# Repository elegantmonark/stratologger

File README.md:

# Stratologger

I'm building an ESP32 payload to record changes in altitude, temperature and motion,
save each run to a microSD card, and show live readings on a small display. The
project combines a custom carrier PCB, removable sensor modules, firmware and a
PETG enclosure. The [contents](#contents) and [repository guide](#repository-guide)
point to the design files, software results and remaining hardware work.

**Author:** Trishan Biswas  
**Project started:** February 2026  
**Status:** Ongoing prototype development

| SL-1 carrier design | Initial system sketch |
|:---:|:---:|
|  |  |
| Current PCB design before manufacture. The ESP32 and sensor modules are not shown. | Original connections and display concept. The custom PCB replaces the drawn breadboard and perfboard stages. |

> [!IMPORTANT]
> **SL-1 is on fabrication hold.** The PCB socket map differs from the common
> 30-pin DOIT ESP32 DevKit V1. Exact module identification, dimensions, pin-map
> correction and rerouting are pending. Do not order the existing Gerber ZIP.
> See [the PCB audit](pcb/SL-1/review/PCB_AUDIT.md).

## Contents

- [SL-1 payload PCB](#sl-1-payload-pcb) · [PCB views](#pcb-views) · [Telemetry validation](#telemetry-validation)
- [Overview](#overview) · [Development](#development) · [Electrical integration](#electrical-integration) · [Display and firmware](#display-and-firmware)
- [Enclosure](#enclosure) · [Data format](#data-format) · [Limitations](#limitations) · [Repository guide](#repository-guide)
- [Next work](#next-work) · [Licence](#licence) · [Building the firmware](#building-the-firmware) · [Reproducing the checks](#reproducing-the-checks)

## SL-1 payload PCB

SL-1 is a two-layer, 90 by 70 mm carrier board. The ESP32 plugs into two 15-pin
female sockets, the AHT20/BMP280 connects through a four-pin male header, and the
GY-521 uses an eight-pin female socket. Four M3 mounting holes support the board
inside the enclosure.

The TFT and its onboard microSD socket mount in the lid and connect through a short
keyed 2x7 harness. Keeping the display separate leaves room for the modules below
and makes it replaceable. The separate TF-card reader is not used.

The [KiCad project](pcb/SL-1/Stratologger_SL1.kicad_pro),
[routed board](pcb/SL-1/Stratologger_SL1.kicad_pcb),
[assembly BOM](pcb/SL-1/manufacturing/assembly-bom.csv) and
[board guide](pcb/SL-1/README.md) are available for review. The design includes
ground planes, an ESP32 antenna keep-out, regulated 5 V input protection and a
single-cell battery-voltage divider.

The audited layout passes KiCad's filled-zone DRC, but the independent pin audit
found that its ESP32 socket assignments do not match the common 30-pin DOIT board.
Passing DRC does not establish the correct module pinout. The existing
[manufacturing outputs](pcb/SL-1/manufacturing/README.md) are historical files;
they will need regenerating after the socket map and routing are corrected.

## PCB views

These are KiCad screenshots of the SL-1 review design before manufacture.
The renders show the carrier, sockets and connectors. The plug-in ESP32, sensor
boards and remote TFT are absent, so these views do not confirm assembled fit.
F1 appears as a footprint because its solid 3D model is not shown.

### Routed layout

### Component renders

| Top view | Angled view |
|:---:|:---:|
|  |  |

## Telemetry validation

I checked the CSV serializer with 100,000 synthetic rows after finding a mismatch
between the checksum calculation and the saved decimal values. The earlier logger
calculated its checksum before rounding the measurements for CSV. That produced
512 checksum mismatches in the test. The revised serializer checks the values
actually written to the file and produced zero mismatches on the same inputs.

All 19 controlled cases met their stated expectations. They cover clean data,
altered measurements, missing and duplicated packets, reordered rows, timing faults,
invalid values, incomplete rows and counter rollover. One case demonstrates that
two changes can cancel under XOR and leave the checksum unchanged.

The [results and method](results/log-validation/README.md) include the
[fault matrix](results/log-validation/fault_matrix.csv), source hashes and limits.
These are software checks with synthetic inputs. Sensor accuracy, SD write
reliability and operation under physical stress still need bench measurements.

## Overview

The payload samples an AHT20/BMP280 combination board and an MPU6050 every 500 ms.
It records temperature, humidity, pressure, barometric altitude, acceleration and
angular velocity, together with packet numbers, timestamps and a checksum.

The work is split into four subsystems:

| Subsystem | Purpose | Current state |
|---|---|---|
| Electrical | Carrier PCB, removable modules and power distribution | SL-1 routed; fabrication held for socket-map correction and measured fit |
| Display | Landscape ST7789V TFT, screen button and onboard SD socket | UI and separate demo compile; physical display and harness checks pending |
| Mechanical | PETG enclosure, module retention, vents and access | Parametric source available; dimensions and printed fit unverified |
| Software | Acquisition, CSV logging, display rendering and host analysis | Firmware builds; synthetic log checks recorded; hardware captures pending |

No assembled payload, battery-endurance result or environmental test run is
currently published.

## Development

The project began in February 2026 with an ESP32, environmental sensing, an IMU,
removable storage and a local display. The first sketch outlined the connections,
screen concept and a path from prototyping to an enclosed payload.

The October firmware baseline brought together sensor acquisition, three display
screens, CSV logging and host validation. The electrical design then moved to the
SL-1 carrier so the modules could remain removable inside the enclosure.

The PCB review exposed the ESP32 socket-map mismatch despite clean routing checks.
The November software checks also exposed the checksum rounding fault described
above. Both findings are recorded in the
[development log](docs/development-log.md) and [validation record](docs/validation.md).

## Electrical integration

| Function | ESP32 pin |
|---|---:|
| I2C SDA / SCL | GPIO21 / GPIO22 |
| VSPI SCK / MOSI / MISO | GPIO18 / GPIO23 / GPIO19 |
| TFT CS / DC / RST | GPIO15 / GPIO2 / GPIO4 |
| SD CS | GPIO5 |
| Screen button | GPIO34 with external 10 kOhm pull-up |
| Battery measurement | GPIO35 through a 100 kOhm / 100 kOhm divider |

These are the intended GPIO functions. The carrier's physical socket positions
still need correcting against the exact ESP32 module. The
[wiring diagram](electrical/wiring-diagram.svg), [netlist](electrical/netlist.csv),
[BOM](electrical/bom.csv) and [assembly guide](electrical/assembly.md) document the
connections and power boundaries.

The environmental header runs `VDD, SDA, GND, SCL`. The display harness must be
matched to the signal names on the actual TFT board; fourteen-pin modules do not
share a universal pin order. TFT and SD use the same SPI bus with separate
chip-select lines.

Standalone power requires a protected single cell and a regulated 5 V supply.
The `5V POWER` input and measurement-only `BAT SENSE` input are separate.
A raw Li-ion or LiPo cell must not be connected directly to the 5 V input.

## Display and firmware

The 2.4-inch ST7789V runs in landscape at 320 by 240 pixels. A single button cycles
between live telemetry, IMU detail and system status. The live view combines an
altitude gauge, a 60-second trace, environmental readings and a simple artificial
horizon. The IMU page shows acceleration and angular-rate traces; the system page
shows raw readings and logging status.

The firmware separates sensor acquisition (`SensorManager`), file handling
(`TelemetryLogger`) and rendering (`DisplayManager`). TFT and SD transfers run
sequentially on the shared SPI bus. Boot faults are reported on the display when
available and through USB serial.

The [display subsystem guide](tft/README.md) includes the cable map and a separate
demo that supplies labelled synthetic values to the UI. Both firmware targets
compile; the display and finished harness still need checking on hardware.

## Enclosure

The [parametric OpenSCAD source](mechanical/enclosure.scad) defines a PETG base and
lid with a display aperture, button opening, sensor vents, PCB supports and USB
access. The carrier mounts in the base and the TFT mounts in the lid.

The dimensions are nominal. Final module heights, TFT mounting holes, battery
holder, cable bends and connector access must be measured before printing. The
[mechanical notes](mechanical/README.md) record the current assumptions.

## Data format

Logs are named `/LOG_001.CSV` through `/LOG_999.CSV` without overwriting an existing
file. Each row follows this schema:

```text
PACKET_ID,TIMESTAMP_MS,TEMP_C,HUMIDITY_PCT,PRESSURE_HPA,ALTITUDE_M,
ACCEL_X_MS2,ACCEL_Y_MS2,ACCEL_Z_MS2,GYRO_X_RADS,GYRO_Y_RADS,
GYRO_Z_RADS,CHECKSUM_HEX
```

The [format example](data/format-example.csv) contains synthetic values. New
hardware captures should include the configuration and conditions recorded in the
[run metadata template](data/run-metadata-template.yaml).

## Limitations

Barometric altitude depends on reference-pressure calibration. Acceleration during
motion distorts the gravity-derived roll and pitch display. The 2 Hz mission log
cannot support a meaningful vibration FFT above 1 Hz; that test needs a separate
acquisition rate.

The XOR checksum misses some combinations of changes. It detects simple corruption
and does not provide authentication. Firmware compilation and host checks also
leave sensor behaviour, supply stability, SD logging and enclosure fit unverified.
The [detailed limits](docs/limitations.md) and [test plan](docs/test-plan.md) cover
the remaining bench, thermal, vibration, impact and endurance work.

## Repository guide

| Location | Contents |
|---|---|
| [`pcb/`](pcb/README.md) | SL-1 KiCad source, review screenshots, audit and manufacturing status |
| [`electrical/`](electrical/assembly.md) | Wiring diagram, netlist, BOM and integration notes |
| [`tft/`](tft/README.md) | Display configuration, screen behaviour and cable map |
| [`mechanical/`](mechanical/README.md) | Parametric enclosure and fit assumptions |
| [`src/`](src/main.cpp) and [`include/`](include/config.h) | ESP32 firmware, display demo and shared configuration |
| [`tools/`](tools/validate_log.py) and [`tests/`](tests/test_repository.py) | CSV analysis, serializer fixture and repository checks |
| [`results/`](results/README.md) | Synthetic telemetry validation and recorded results |
| [`data/`](data/README.md) | CSV example and capture metadata template |
| [`docs/`](docs/development-log.md) | Development, architecture, validation, limits and test plans |
| [`hardware/`](hardware/README.md) | Physical build state and future hardware evidence |

## Next work

1. Confirm the exact ESP32 pinout and measure all module headers and body clearances.
2. Correct the SL-1 socket map and routing, repeat the electrical review and regenerate manufacturing files.
3. Assemble one board and check power, boot, sensors, TFT, SD and the display harness.
4. Fit the enclosure around the measured assembly and standalone power system.
5. Publish repeat captures and physical test results with their build configurations.

## Licence

The firmware, hardware documentation and mechanical source are released under the
Apache License 2.0 in [`LICENSE`](LICENSE).

## Building the firmware

Install the PlatformIO extension for Visual Studio Code and open the repository
root. Build, upload and open the serial monitor with:

```bash
pio run -e esp32dev
pio run -e esp32dev --target upload
pio device monitor
```

The [PlatformIO configuration](platformio.ini) selects the Arduino framework,
dependencies and TFT_eSPI pin settings. The installed library's `User_Setup.h`
does not need editing. To build the display-only demo:

```bash
pio run -e display-demo
```

## Reproducing the checks

Run the host checks from the repository root:

```bash
python -m unittest discover -s tools -p 'test_*.py' -v
python -m unittest discover -s tests -v
python tools/validate_log.py data/format-example.csv
```

The [telemetry validation instructions](results/log-validation/README.md#run-it-again)
explain how to compile the C++ serializer fixture and regenerate the controlled
cases and plots. PCB review and fabrication requirements are documented separately
in the [SL-1 board guide](pcb/SL-1/README.md).

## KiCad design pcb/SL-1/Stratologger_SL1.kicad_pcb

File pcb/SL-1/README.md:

# Stratologger SL-1 PCB

> **FABRICATION HOLD — 27 October 2026:** the existing ESP32 socket map does
> not match the common 30-pin DOIT DevKit V1. The exact module has not yet been
> confirmed. Do not order the existing Gerber ZIP. See [the audit](review/PCB_AUDIT.md).
> `release-status.json` blocks the fabrication script until the pin map and routing
> have been corrected and reviewed. The current board contains the new silkscreen logo.

SL-1 is a 90 by 70 mm, two-layer carrier board for the Stratologger payload. The
ESP32 and sensors remain replaceable, while the TFT and its onboard microSD socket
mount in the enclosure lid and connect through a short keyed harness.

## Board layout

- 30-pin ESP32 DevKit V1 on two 1x15 female sockets, with USB at the board edge.
- AHT20/BMP280 on a 1x4 male header ordered `VDD, SDA, GND, SCL`.
- GY-521 on a 1x8 female socket ordered `VCC, GND, SCL, SDA, XDA, XCL, AD0, INT`.
- Keyed 2x7 IDC connector for the lid-mounted TFT and onboard microSD socket.
- Header for the lid-mounted screen button and its required GPIO34 pull-up.
- Fused, Schottky-isolated regulated 5 V input and a separate battery-sense input.
- Ground planes on both copper layers and a copper keep-out below the ESP32 antenna.
- Four 3.2 mm non-plated mounting holes for M3 hardware.

The AHT20/BMP280 pin legend sits beside the header, outside the nominal breakout
outline, so the module should not cover it when plugged in. Check the exact module
overhang against the 1:1 board print.

The separate TF-card reader is not used. CSV logging uses the card socket already
fitted to the TFT module.

### ESP32 socket order

The following is the **legacy assumed map in the current file**, not a confirmed
DevKit V1 pinout. With USB facing the lower edge, both socket rows start at the
end opposite USB. The common DOIT module differs from this map:

| Socket | Pin order |
|---|---|
| Left (J1) | 3V3, EN, GPIO36, GPIO39, GPIO34, GPIO35, GPIO32, GPIO33, GPIO25, GPIO26, GPIO27, GPIO14, GPIO12, GND, VIN |
| Right (J2) | GND, GPIO23, GPIO22, GPIO1, GPIO3, GPIO21, GND, GPIO19, GPIO18, GPIO5, GPIO17, GPIO16, GPIO4, GPIO2, GPIO15 |

The intended GPIO functions match the firmware, but the socket positions below
must be corrected against the actual module before they can implement those functions.

## Electrical review

KiCad 10 reports:

- 0 DRC violations;
- 0 unconnected pads; and
- 0 footprint errors.

The historical report is in `manufacturing/Stratologger_SL1-drc.rpt`; the latest
logo-board report is in `review/logo-board-drc.rpt`. Passing DRC confirms
the routed board against the configured electrical rules; it does not prove that a
generic plug-in module has the same body dimensions as the one on hand.

## Required physical fit check

Do this before uploading the Gerber ZIP to a fabricator:

1. Print `Stratologger_SL1.kicad_pcb` from KiCad at exactly 1:1 scale.
2. Confirm the ESP32 has 30 pins and 25.4 mm between its two header rows.
3. Place the exact ESP32, AHT20/BMP280 and GY-521 over the print.
4. Check every pin-1 position, header order, module overhang and USB clearance.
5. Confirm the enclosure can accept the 90 by 70 mm outline and M3 hole centres.
6. Check the display harness pin map in `../../tft/README.md` with a multimeter.

If any module does not align, edit the source and regenerate the release package;
do not bend module pins to force a fit.

## Files

- `Stratologger_SL1.kicad_pcb`: editable routed KiCad board.
- `Stratologger_SL1.kicad_pro`: KiCad project settings.
- `generate_stratologger_pcb.py`: reproducible board generator.
- `manufacturing/`: Gerbers, drill files, DRC report, assembly BOM and order notes.
- `manufacturing/Stratologger_SL1-fabrication.zip`: file to upload after the fit check.

## Regenerating

The generator retains the unverified legacy map. Regenerating it does not resolve
the fabrication hold. Use `audit_board.py` to expose the module-map mismatch;
exit code 2 denotes the pending fabrication hold.

Run from this directory with KiCad 10 installed:

```powershell
& "C:\Program Files\KiCad\10.0\bin\python.exe" .\generate_stratologger_pcb.py
& "C:\Program Files\KiCad\10.0\bin\kicad-cli.exe" pcb drc --refill-zones --output .\manufacturing\Stratologger_SL1-drc.rpt .\Stratologger_SL1.kicad_pcb
```

The fabrication defaults are 2 layers, 1.6 mm FR-4, 1 oz copper, lead-free HASL,
green solder mask and white silkscreen. No controlled impedance, castellations,
edge plating or via-in-pad process is required.

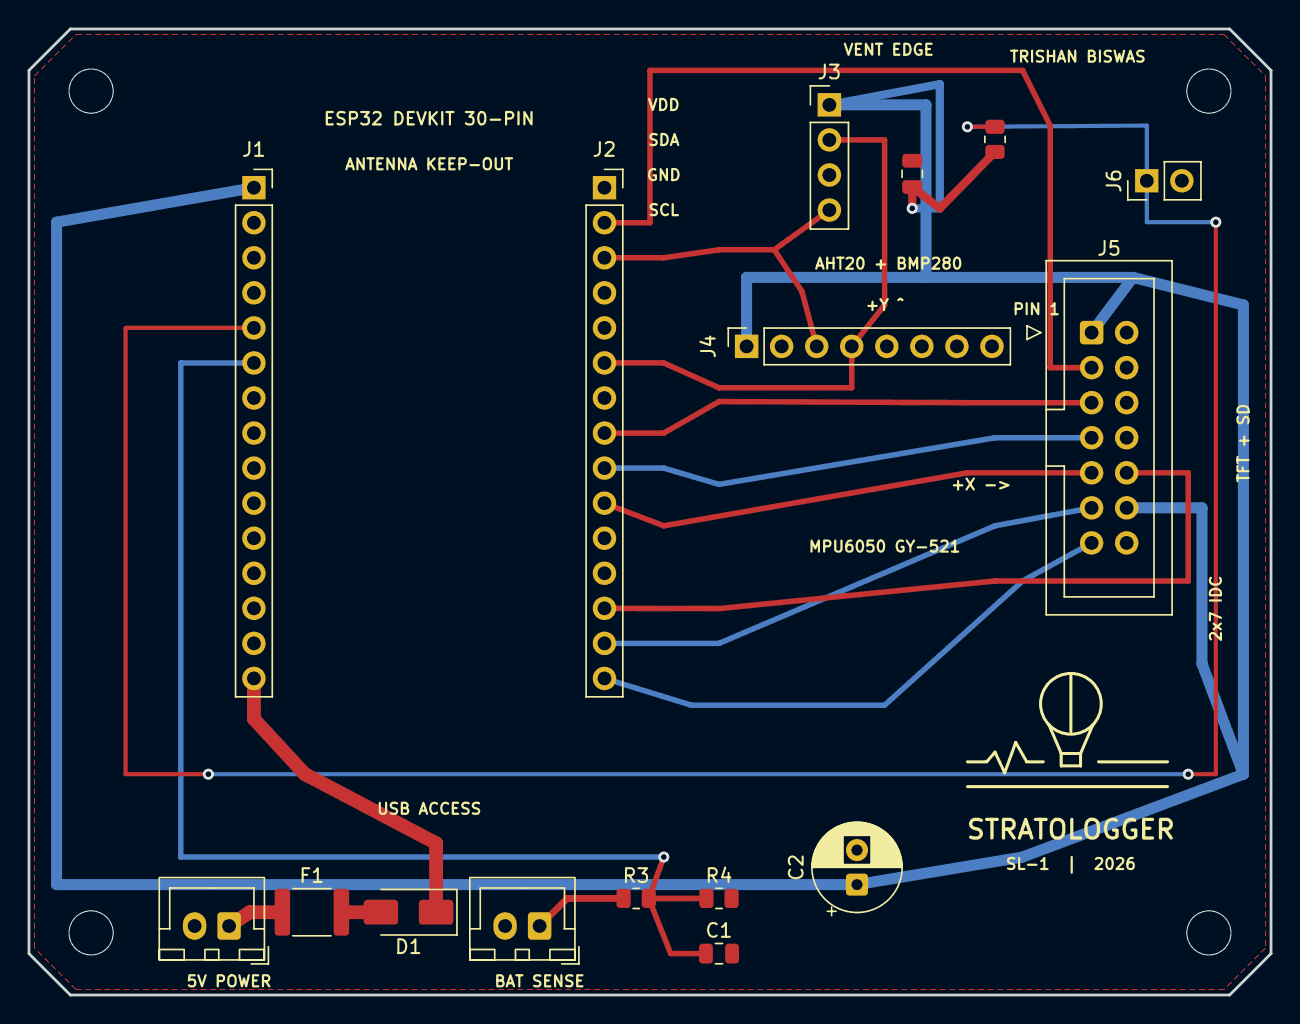
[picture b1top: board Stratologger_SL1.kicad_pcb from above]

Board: 2 copper layers, 90.0 x 70.0 mm, 20 parts (0 on the bottom side), 17 nets.

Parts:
C1, C3: 100nF; C_0805_2012Metric
C2: 100uF 6.3V; CP_Radial_D6.3mm_P2.50mm
D1: SS34; D_SMA
F1: 0.75A PTC; Fuse_1812_4532Metric
H1, H2, H3, H4: M3; MountingHole_3.2mm_M3
J1: ESP32_LEFT; PinSocket_1x15_P2.54mm_Vertical
J2: ESP32_RIGHT; PinSocket_1x15_P2.54mm_Vertical
J3: AHT20_BMP280; PinHeader_1x04_P2.54mm_Vertical
J4: MPU6050_GY521; PinSocket_1x08_P2.54mm_Vertical
J5: REMOTE_TFT_SD; IDC-Header_2x07_P2.54mm_Vertical
J6: REMOTE_BUTTON; PinHeader_1x02_P2.54mm_Vertical
J7: REGULATED_5V_IN; JST_XH_B2B-XH-A_1x02_P2.50mm_Vertical
J8: BATTERY_SENSE_ONLY; JST_XH_B2B-XH-A_1x02_P2.50mm_Vertical
R2: 10k BUTTON PULLUP; R_0805_2012Metric
R3, R4: 100k 1%; R_0805_2012Metric

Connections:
+3V3: C2.1, C3.1, J1.1, J3.1, J4.1, J5.1, J5.12, R2.1
+5V_EXT: F1.1, J7.1
+5V_FUSED: D1.2, F1.2
BATTERY_SENSE: C1.1, J1.6, R3.2, R4.1
BAT_RAW: J8.1, R3.1
GND: C1.2, C2.2, C3.2, J1.14, J2.1, J2.7, J3.3, J4.2, J5.2, J5.4, J5.6, J5.8, J5.14, J6.2, J7.2, J8.2, R4.2
I2C_SCL: J2.3, J3.4, J4.3
I2C_SDA: J2.6, J3.2, J4.4
SCREEN_BUTTON: J1.5, J6.1, R2.2
SD_CS: J2.10, J5.9
SPI_MISO: J2.8, J5.5
SPI_MOSI: J2.2, J5.3
SPI_SCK: J2.9, J5.7
TFT_CS: J2.15, J5.13
TFT_DC: J2.14, J5.11
TFT_RST: J2.13, J5.10
VIN_5V: D1.1, J1.15

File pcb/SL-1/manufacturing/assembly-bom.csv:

Reference,Quantity,Value,Package,Populate,Assembly note
R2,1,10 kohm 1 percent,0805,Yes,GPIO34 pull-up
R3-R4,2,100 kohm 1 percent,0805,Yes,Battery divider
C1,1,100 nF X7R 10 V or higher,0805,Yes,ADC filter
C2,1,100 uF 6.3 V low ESR,Radial 6.3 mm body 2.5 mm pitch,Yes,Observe polarity
C3,1,100 nF X7R 10 V or higher,0805,Yes,Environmental sensor decoupling
F1,1,750 mA resettable PTC,1812,Yes,External 5 V input protection
D1,1,SS34,SMA,Yes,Observe cathode marking
J1-J2,2,1x15 female socket,2.54 mm vertical,Yes,ESP32 row spacing is 25.4 mm
J3,1,1x4 male header,2.54 mm vertical,Yes,VDD SDA GND SCL from pin 1
J4,1,1x8 female socket,2.54 mm vertical,Yes,GY-521 socket
J5,1,2x7 keyed box header,2.54 mm vertical,Yes,Align pin-1 triangle with PCB mark
J6,1,1x2 male header,2.54 mm vertical,Yes,Remote screen button
J7-J8,2,JST-XH 2-pin header,2.50 mm vertical,Yes,Check polarity before mating
H1-H4,4,M3 clearance hole,3.2 mm NPTH,N/A,No component

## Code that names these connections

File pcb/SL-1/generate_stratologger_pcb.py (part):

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        31.5,
        {
            "1": nets["+3V3"],          # 3V3
            "5": nets["SCREEN_BUTTON"], # GPIO34
            "6": nets["BATTERY_SENSE"], # GPIO35
            "14": nets["GND"],
            "15": nets["VIN_5V"],
        },
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        31.5,
        {
            "1": nets["GND"],
            "2": nets["SPI_MOSI"],       # GPIO23
            "3": nets["I2C_SCL"],        # GPIO22
            "6": nets["I2C_SDA"],        # GPIO21
            "7": nets["GND"],
            "8": nets["SPI_MISO"],       # GPIO19
            "9": nets["SPI_SCK"],        # GPIO18
            "10": nets["SD_CS"],         # GPIO5
            "13": nets["TFT_RST"],       # GPIO4
            "14": nets["TFT_DC"],        # GPIO2
            "15": nets["TFT_CS"],        # GPIO15
        },
    )

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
